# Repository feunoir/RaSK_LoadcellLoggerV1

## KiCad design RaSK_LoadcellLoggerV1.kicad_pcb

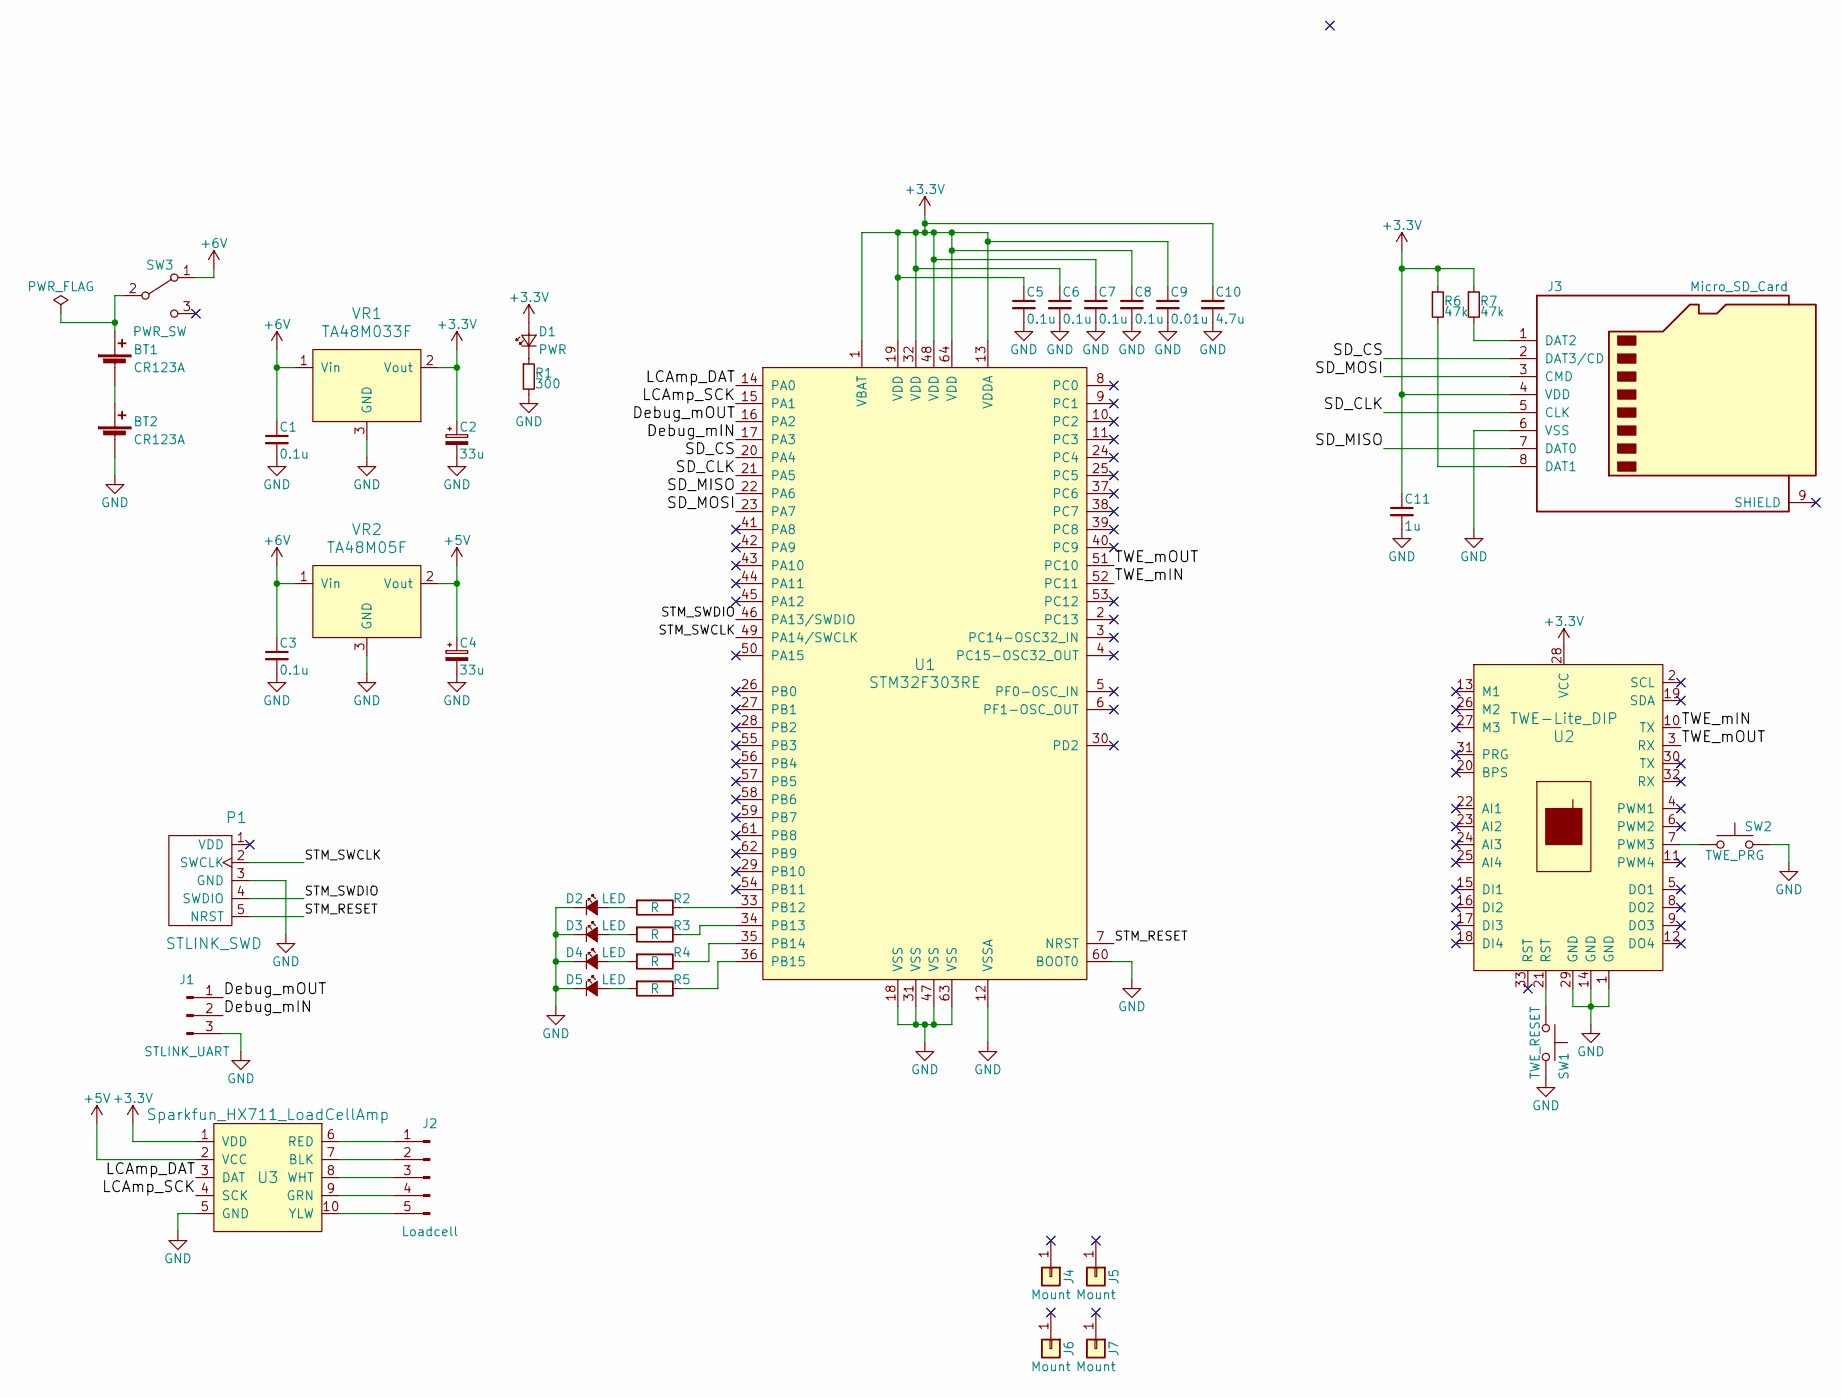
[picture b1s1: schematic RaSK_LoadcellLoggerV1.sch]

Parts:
BT1, BT2: CR123A; BHC-CR123A
C1, C3, C5, C6, C7, C8: 0.1u; C_0603
C2, C4: 33u; CP_Radial_D10.0mm_P2.50mm
C9: 0.01u; C_0603
C10: 4.7u; C_1206
C11: 1u; C_0603
D1: PWR; LED_D3.0mm
D2, D3, D4, D5: LED; LED_D3.0mm
J1: STLINK_UART; DF1E-3P_Straight
J2: Loadcell; DF1E-5P_Straight
J3: Micro_SD_Card; AE-MICRO-SD-DIP
J4, J5, J6, J7: Mount; MountingHole_3.2mm_M3
P1: STLINK_SWD; DF1E-5P_Straight
R1: 300; R_0603
R2, R3, R4, R5: R; R_0603
R6, R7: 47k; R_0603
SW1: TWE_RESET; TactSwitch_1
SW2: TWE_PRG; TactSwitch_1
SW3: PWR_SW; ToggleSeitch_Q22
U1: STM32F303RE; LQFP-64_10x10mm_Pitch0.5mm
U2: TWE-Lite_DIP
U3: Sparkfun_HX711_LoadCellAmp; Sparkfun_HX711_LoadCellAmp_Module
VR1: TA48M033F; TA48Mxx
VR2: TA48M05F; TA48Mxx

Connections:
+3V3: C2.1, C5.1, C6.1, C7.1, C8.1, C9.1, C10.1, C11.1, D1.2 (A), J3.4 (VDD), R6.1, R7.1, U1.1 (VBAT), U1.13 (VDDA), U1.19 (VDD), U1.32 (VDD), U1.48 (VDD), U1.64 (VDD), U2.28 (VCC), U3.1 (VDD), VR1.2 (Vout)
+5V: C4.1, U3.2 (VCC), VR2.2 (Vout)
+6V: C1.1, C3.1, SW3.1 (A), VR1.1 (Vin), VR2.1 (Vin)
/Debug_mIN: J1.2, U1.17 (PA3)
/Debug_mOUT: J1.1, U1.16 (PA2)
/LCAmp_DAT: U1.14 (PA0), U3.3 (DAT)
/LCAmp_SCK: U1.15 (PA1), U3.4 (SCK)
/SD_CLK: J3.5 (CLK), U1.21 (PA5)
/SD_CS: J3.2 (DAT3/CD), U1.20 (PA4)
/SD_MISO: J3.7 (DAT0), U1.22 (PA6)
/SD_MOSI: J3.3 (CMD), U1.23 (PA7)
/STM_RESET: P1.5 (NRST), U1.7 (NRST)
/STM_SWCLK: P1.2 (SWCLK), U1.49 (PA14/SWCLK)
/STM_SWDIO: P1.4 (SWDIO), U1.46 (PA13/SWDIO)
/TWE_mIN: U1.52 (PC11), U2.10 (TX)
/TWE_mOUT: U1.51 (PC10), U2.3 (RX)
GND: BT2.2 (-), C1.2, C2.2, C3.2, C4.2, C5.2, C6.2, C7.2, C8.2, C9.2, C10.2, C11.2, D2.1 (K), D3.1 (K), D4.1 (K), D5.1 (K), J1.3, J3.6 (VSS), P1.3 (GND), R1.2, SW1.2, SW2.2, U1.12 (VSSA), U1.18 (VSS), U1.31 (VSS), U1.47 (VSS), U1.60 (BOOT0), U1.63 (VSS), U2.1 (GND), U2.14 (GND), U2.29 (GND), U3.5 (GND), VR1.3 (GND), VR2.3 (GND)
unnamed: BT1.1 (+), SW3.2 (B)
unnamed: BT1.2 (-), BT2.1 (+)
unnamed: D1.1 (K), R1.1
unnamed: D2.2 (A), R2.2
unnamed: D3.2 (A), R3.2
unnamed: D4.2 (A), R4.2
unnamed: D5.2 (A), R5.2
unnamed: J2.1, U3.6 (RED)
unnamed: J2.2, U3.7 (BLK)
unnamed: J2.3, U3.8 (WHT)
unnamed: J2.4, U3.9 (GRN)
unnamed: J2.5, U3.10 (YLW)
unnamed: J3.1 (DAT2), R7.2
unnamed: J3.8 (DAT1), R6.2
unnamed: R2.1, U1.33 (PB12)
unnamed: R3.1, U1.34 (PB13)
unnamed: R4.1, U1.35 (PB14)
unnamed: R5.1, U1.36 (PB15)
unnamed: SW1.1, U2.21 (RST)
unnamed: SW2.1, U2.7 (PWM3)

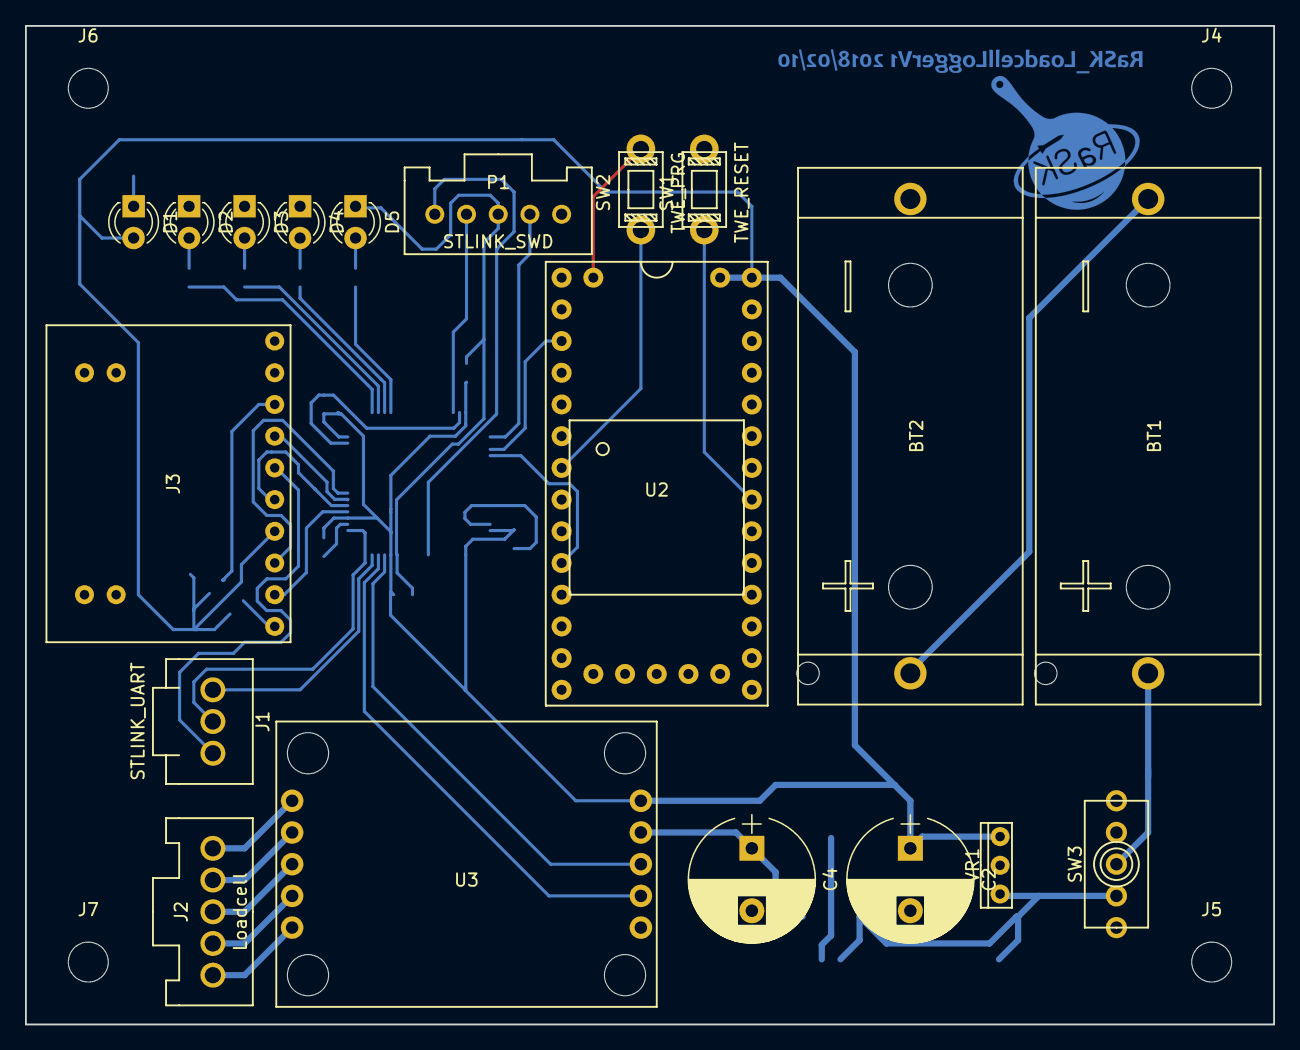
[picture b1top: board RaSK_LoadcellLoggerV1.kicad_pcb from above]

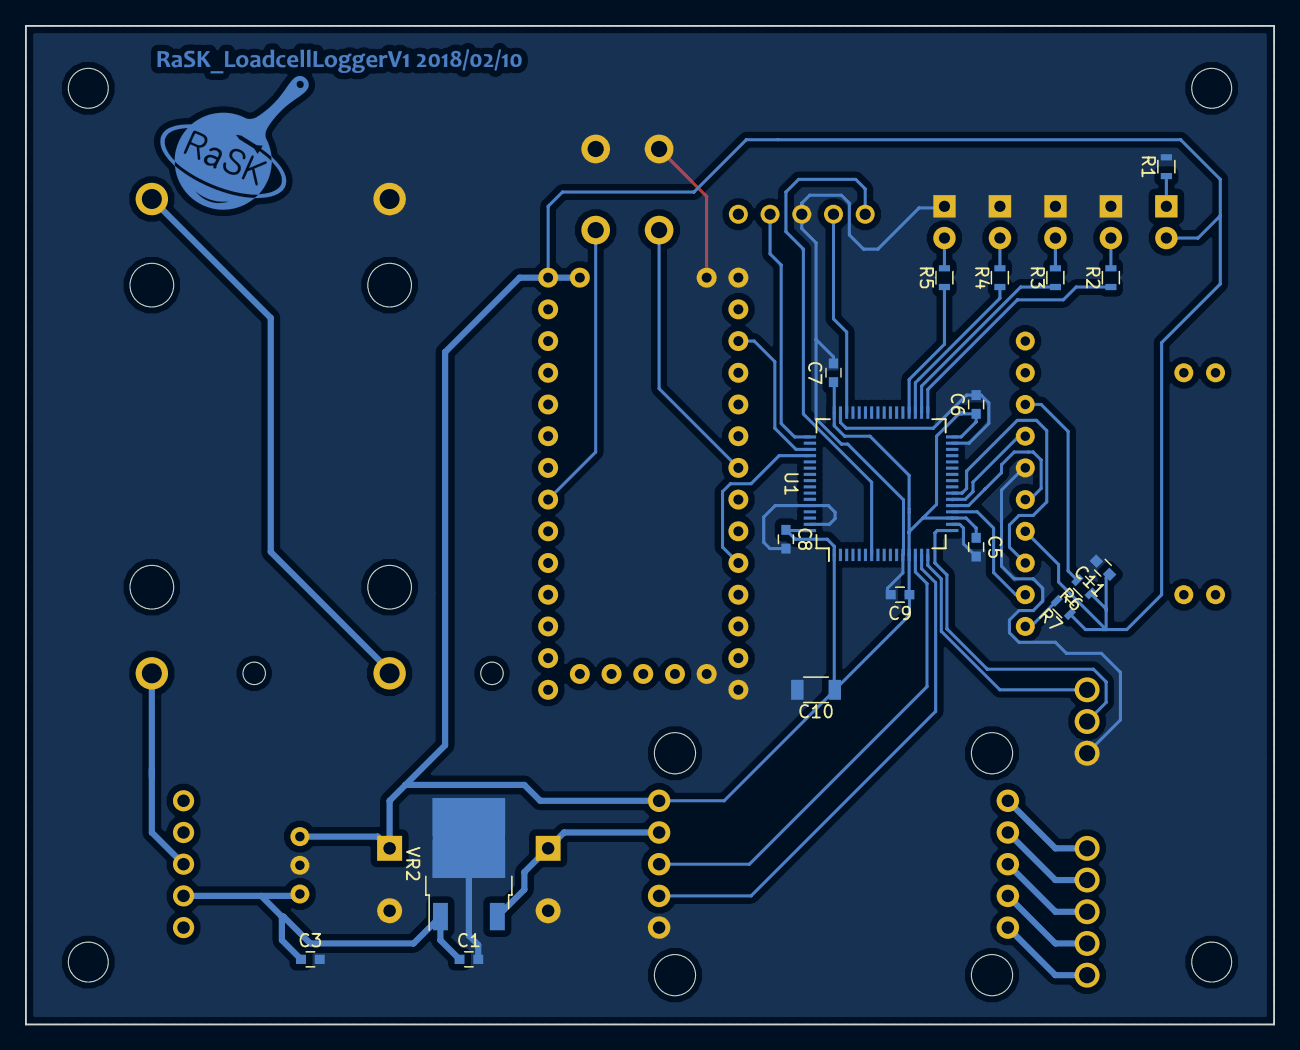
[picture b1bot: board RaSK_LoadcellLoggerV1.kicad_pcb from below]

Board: 2 copper layers, 100.0 x 80.0 mm, 41 parts (18 on the bottom side), 37 nets.

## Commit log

2018-02-06 I added components and footprint library to the project.
2018-02-06 I added MCU, Power Supply, SWD Connector, SDCard and some circuits necessary for operation.
2018-02-07 add 4 led status indicators
2018-02-07 fix incorrect project name RsSK→RaSK
2018-02-07 library linking testo
2018-02-07 add .gitignore
2018-02-08 complete making schematic
2018-02-08 connect stm32 pins to other components except for loadcell-amp (Sorry, I forgot this step...) add STLink UART debug connector add two buttons for TWE-Lite programming
    p.s.
    I didn't connect communication pins of loadcell-amp.
    These pins can connect any stm32 digital pins.
    Please connect these pins as you want.
2018-02-08 fix connector J2 name
2018-02-08 reflect library changes
2018-02-09 add power switch ,pass capacitor and assign footprint
2018-02-09 change micro sd card slot to dip
2018-02-09 create pcb file
2018-02-10 fix footprint of regulator and capasitor
